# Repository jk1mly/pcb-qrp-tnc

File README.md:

# pcb-qrp-tnc
おもちゃのトランシーバ用のIC;BK4802Pを使ったモノバンドのFX.25対応TNC付き無線機
TNC部分はM5stamp

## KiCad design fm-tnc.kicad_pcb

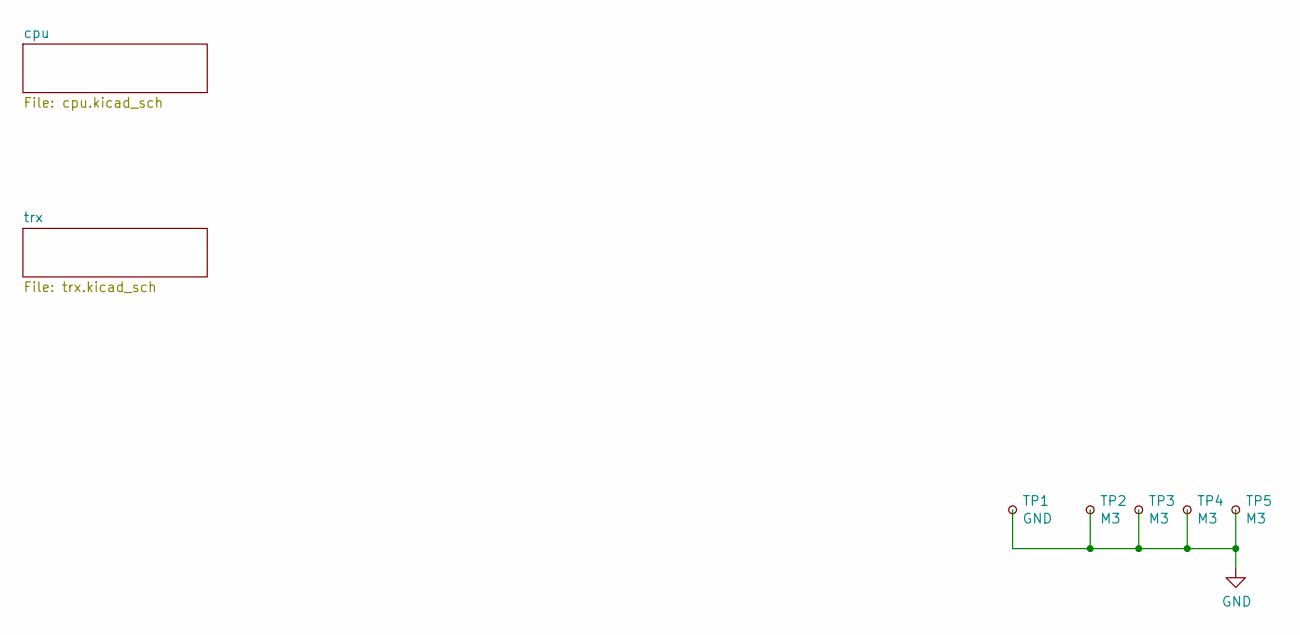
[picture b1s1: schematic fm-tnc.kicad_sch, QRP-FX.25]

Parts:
TP1: GND; PinHeader_1x01_P2.54mm_Vertical
TP2, TP3, TP4, TP5: M3; MountingHole_3.5mm_Pad

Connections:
GND: TP1.1, TP2.1, TP3.1, TP4.1, TP5.1; also elsewhere on the board

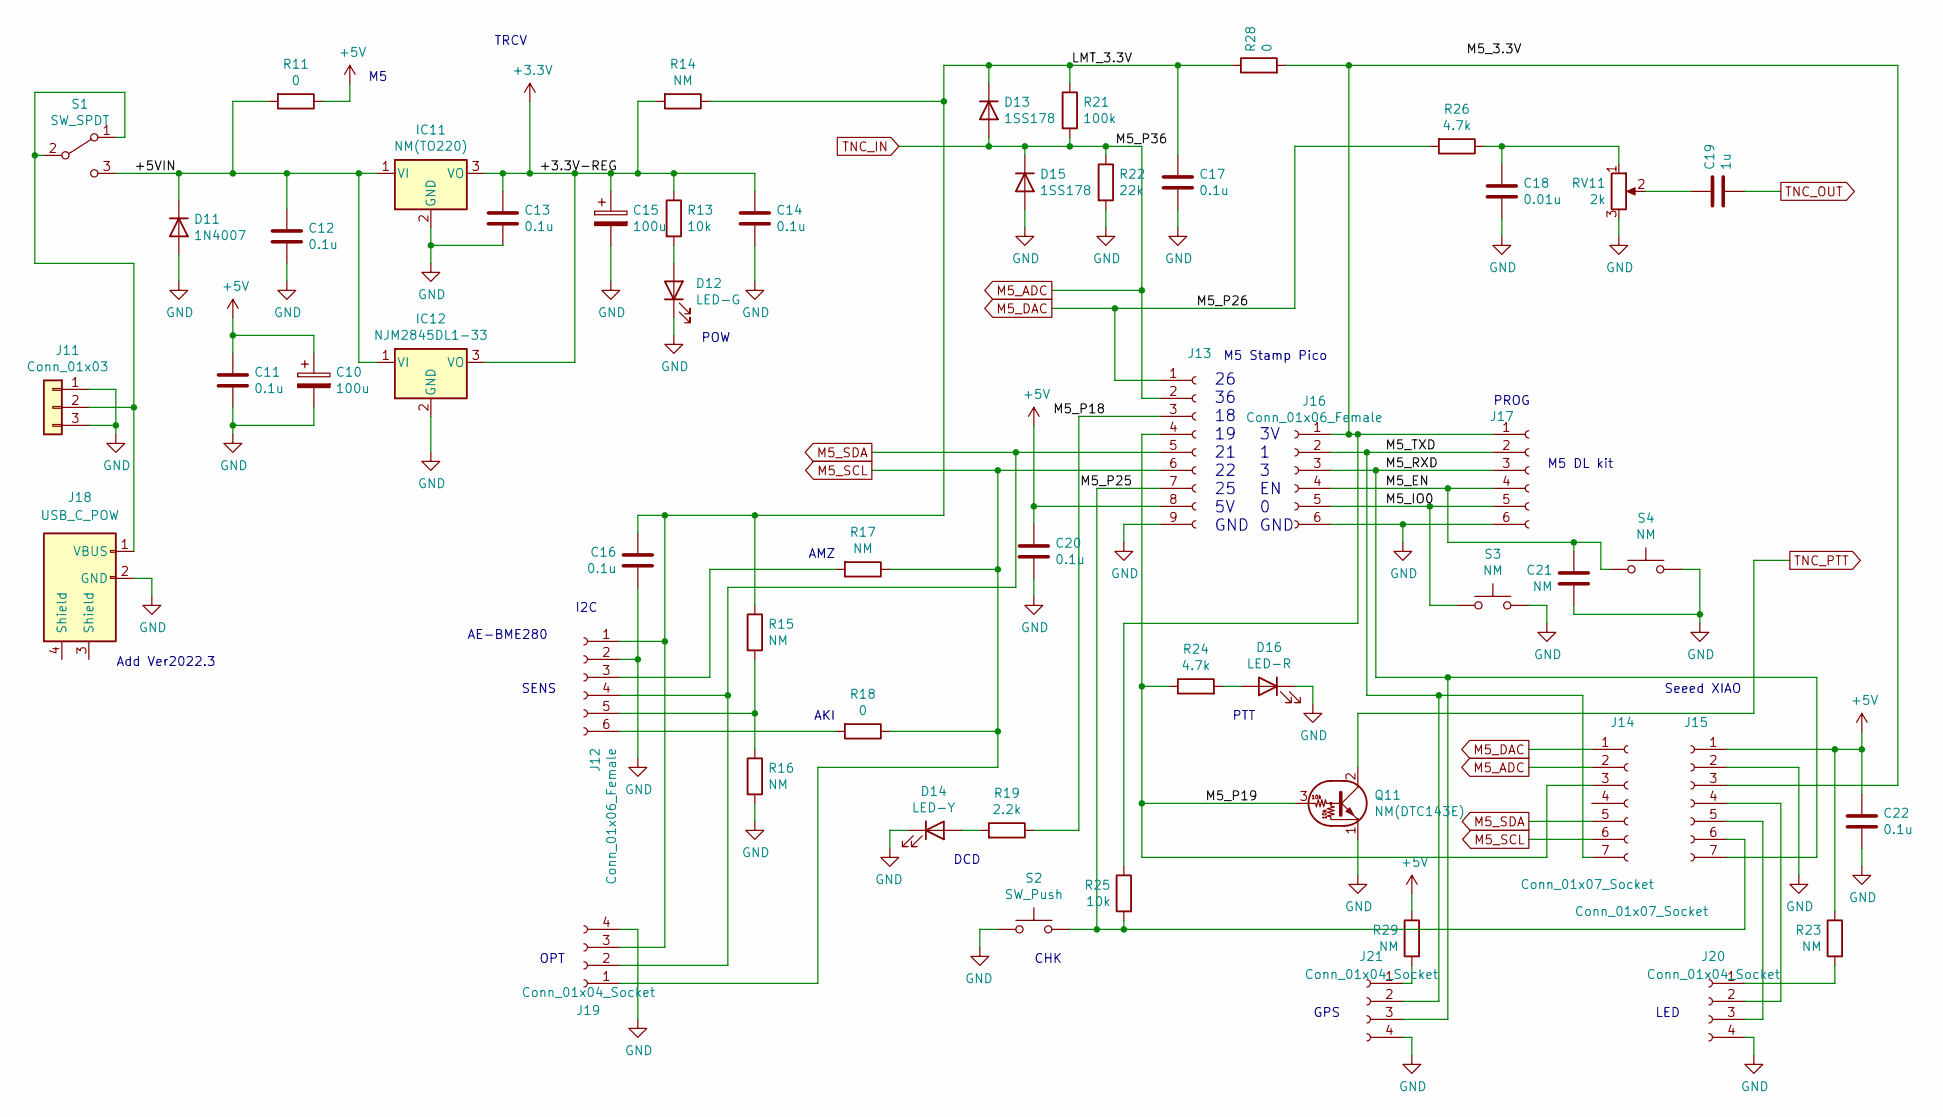
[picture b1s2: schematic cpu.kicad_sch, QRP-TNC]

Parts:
C10, C15: 100u; CP_Radial_D4.0mm_P2.00mm
C11, C12, C13, C14, C16, C17, C20, C22: 0.1u; C_Disc_D3.4mm_W2.1mm_P2.50mm
C18: 0.01u; C_Disc_D3.4mm_W2.1mm_P2.50mm
C19: 1u; C_Disc_D3.4mm_W2.1mm_P2.50mm
C21: NM; C_Disc_D3.4mm_W2.1mm_P2.50mm
D11: 1N4007; D_DO-41_SOD81_P10.16mm_Horizontal
D12: LED-G; LED_3mm_Radial
D13, D15: 1SS178; D_A-405_P2.54mm_Vertical_AnodeUp
D14: LED-Y; LED_3mm_Radial
D16: LED-R; LED_3mm_Radial
IC11: NM(TO220); TO-126-3_Vertical
IC12: NJM2845DL1-33; TO-252-3
J11: Conn_01x03; PinHeader_1x03_P2.54mm_Vertical
J12, J16, J17: Conn_01x06_Female; PinHeader_1x06_P2.54mm_Vertical
J13: Conn_01x09_Female; PinHeader_1x09_P2.54mm_Vertical
J14, J15: Conn_01x07_Socket; PinHeader_1x07_P2.54mm_Vertical
J18: USB_C_POW
J19, J20, J21: Conn_01x04_Socket; PinHeader_1x04_P2.54mm_Vertical
Q11: NM(DTC143E); TO-92_Inline_Wide
R11, R18, R28: 0; R_Axial_DIN0207_L6.3mm_D2.5mm_P2.54mm_Vertical
R13, R25: 10k; R_Axial_DIN0207_L6.3mm_D2.5mm_P2.54mm_Vertical
R14, R15, R16, R17, R23, R29: NM; R_Axial_DIN0207_L6.3mm_D2.5mm_P2.54mm_Vertical
R19: 2.2k; R_Axial_DIN0207_L6.3mm_D2.5mm_P2.54mm_Vertical
R21: 100k; R_Axial_DIN0207_L6.3mm_D2.5mm_P2.54mm_Vertical
R22: 22k; R_Axial_DIN0207_L6.3mm_D2.5mm_P2.54mm_Vertical
R24, R26: 4.7k; R_Axial_DIN0207_L6.3mm_D2.5mm_P2.54mm_Vertical
RV11: 2k; Potentiometer_Bourns_3386P_Vertical
S1: SW_SPDT; Switch_Slide_11.6x4mm_EG1218
S2: SW_Push; Switch_2P
S3, S4: NM; Switch_2P

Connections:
+3V3: C13.1, C14.1, C15.1, IC11.3 (VO), IC12.3 (VO), R13.1, R14.2; also elsewhere on the board
+5V: C10.1, C11.1, C20.1, C22.1, J13.8, J15.1, R11.1, R23.1, R29.1
/cpu/+5VIN: C12.1, D11.1 (K), IC11.1 (VI), IC12.1 (VI), R11.2, S1.3 (C)
/cpu/LMT_3.3V: C16.1, C17.1, D13.1 (K), J12.1, J19.3, R14.1, R15.1, R21.1, R28.1
/cpu/M5_EN: C21.1, J16.4, J17.4, S4.1
/cpu/M5_IO0: J16.5, J17.5, S3.1
/cpu/M5_P18: J13.3, R19.1
/cpu/M5_P19: J13.4, J14.3, Q11.3 (B), R24.1
/cpu/M5_P25: J13.7, J15.6, R25.2, S2.1
/cpu/M5_RXD: J15.7, J16.3, J17.3, J21.3
/cpu/M5_TXD: J14.7, J16.2, J17.2, J21.2
GND: C10.2, C11.2, C12.2, C13.2, C14.2, C15.2, C16.2, C17.2, C18.2, C20.2, C21.2, C22.2, D11.2 (A), D12.1 (K), D14.1 (K), D15.2 (A), D16.1 (K), IC11.2 (GND), IC12.2 (GND), J11.1, J11.3, J12.2, J13.9, J15.2, J16.6, J17.6, J18.2 (GND), J19.4, J20.4, J21.4, Q11.1 (E), R16.2, R22.2, RV11.3, S2.2, S3.2, S4.2; also elsewhere on the board
M5_ADC: D13.2 (A), D15.1 (K), J13.2, J14.2, R21.2, R22.1; also elsewhere on the board
M5_DAC: J13.1, J14.1, R26.2
M5_SCL: J13.6, J14.6, J19.1, R17.1, R18.1; also elsewhere on the board
M5_SDA: J12.4, J13.5, J14.5, J19.2; also elsewhere on the board
unnamed: C18.1, R26.1, RV11.1
unnamed: C19.1, RV11.2
unnamed: D12.2 (A), R13.2
unnamed: D14.2 (A), R19.2
unnamed: D16.2 (A), R24.2
unnamed: J11.2, J18.1 (VBUS), S1.1 (A), S1.2 (B)
unnamed: J12.3, R17.2
unnamed: J12.5, R15.2, R16.1
unnamed: J12.6, R18.2
unnamed: J15.3, J16.1, J17.1, R25.1, R28.2
unnamed: J15.4, J20.2
unnamed: J15.5, J20.3
unnamed: J20.1, R23.2
unnamed: J21.1, R29.2
TNC_OUT: C19.2; also elsewhere on the board
TNC_PTT: Q11.2 (C); also elsewhere on the board

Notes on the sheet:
DCD
PTT
SENS
OPT
AKI
CHK
3V 1 3 EN 0 GND
AMZ
26 36 18 19 21 22 25 5V GND
AE-BME280
M5 Stamp Pico
Add Ver2022.3
PROG
I2C
POW
TRCV
Seeed XIAO
M5 DL kit
GPS
LED

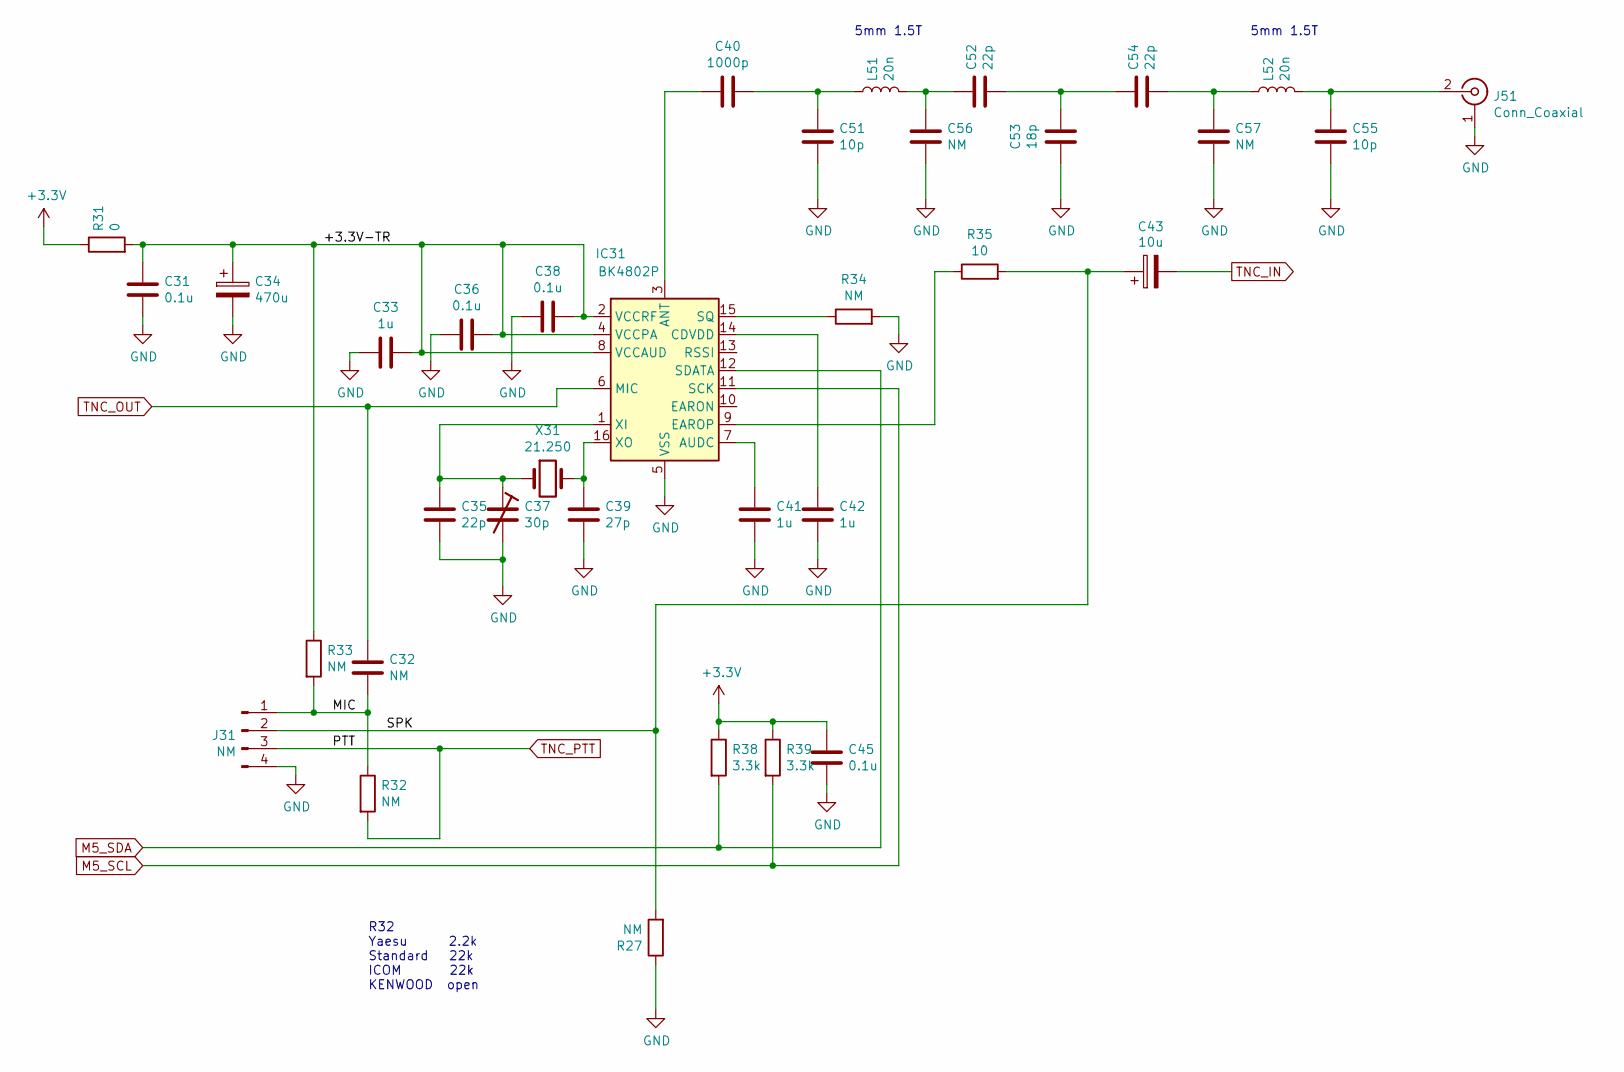
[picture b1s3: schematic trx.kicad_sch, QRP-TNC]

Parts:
C31, C36, C38, C45: 0.1u; C_Disc_D3.4mm_W2.1mm_P2.50mm
C32, C56, C57: NM; C_Disc_D3.4mm_W2.1mm_P2.50mm
C33, C41, C42: 1u; C_Disc_D3.4mm_W2.1mm_P2.50mm
C34: 470u; CP_Radial_D8.0mm_P3.50mm
C35, C52, C54: 22p; C_Disc_D3.4mm_W2.1mm_P2.50mm
C37: 30p; C_TRIM_P6.00mm
C39: 27p; C_Disc_D3.4mm_W2.1mm_P2.50mm
C40: 1000p; C_Disc_D3.4mm_W2.1mm_P2.50mm
C43: 10u; CP_Radial_D5.0mm_P2.00mm
C51, C55: 10p; C_Disc_D3.4mm_W2.1mm_P2.50mm
C53: 18p; C_Disc_D3.4mm_W2.1mm_P2.50mm
IC31: BK4802P; SO-16_3.9x9.9mm_P1.27mm
J31: NM; PinHeader_1x04_P2.54mm_Vertical
J51: Conn_Coaxial; RF_SMA_Vertical_5-1814832-1
L51, L52: 20n; coil3_7mm
R27, R32, R33, R34: NM; R_Axial_DIN0207_L6.3mm_D2.5mm_P2.54mm_Vertical
R31: 0; R_Axial_DIN0207_L6.3mm_D2.5mm_P2.54mm_Vertical
R35: 10; R_Axial_DIN0207_L6.3mm_D2.5mm_P2.54mm_Vertical
R38, R39: 3.3k; R_Axial_DIN0207_L6.3mm_D2.5mm_P2.54mm_Vertical
X31: 21.250; HC49

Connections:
+3V3: C45.1, R31.1, R38.1, R39.1; also elsewhere on the board
/trx/+3.3V-TR: C31.1, C33.2, C34.1, C36.2, C38.2, IC31.2 (VCCRF), IC31.4 (VCCPA), IC31.8 (VCCAUD), R31.2, R33.1
/trx/MIC: C32.2, J31.1, R32.1, R33.2
/trx/SPK: C43.1, J31.2, R27.2, R35.2
GND: C31.2, C33.1, C34.2, C35.2, C36.1, C37.2, C38.1, C39.2, C41.2, C42.2, C45.2, C51.2, C53.1, C55.2, C56.2, C57.2, IC31.5 (VSS), J31.4, J51.1 (G), R27.1, R34.2; also elsewhere on the board
M5_ADC: C43.2; also elsewhere on the board
M5_SCL: IC31.11 (SCK), R39.2; also elsewhere on the board
M5_SDA: IC31.12 (SDATA), R38.2; also elsewhere on the board
unnamed: C40.2, C51.1, L51.1
unnamed: C52.1, C56.1, L51.2
unnamed: C52.2, C53.2, C54.1
unnamed: C54.2, C57.1, L52.1
unnamed: C40.1, IC31.3 (ANT)
unnamed: C41.1, IC31.7 (AUDC)
unnamed: C42.1, IC31.14 (CDVDD)
unnamed: IC31.9 (EAROP), R35.1
unnamed: IC31.15 (SQ), R34.1
unnamed: C35.1, C37.1, IC31.1 (XI), X31.1
unnamed: C39.1, IC31.16 (XO), X31.2
unnamed: C55.1, J51.2 (S), L52.2
TNC_OUT: C32.1, IC31.6 (MIC); also elsewhere on the board
TNC_PTT: J31.3, R32.2; also elsewhere on the board

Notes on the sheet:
R32 Yaesu 2.2k Standard 22k ICOM 22k KENWOOD open
5mm 1.5T

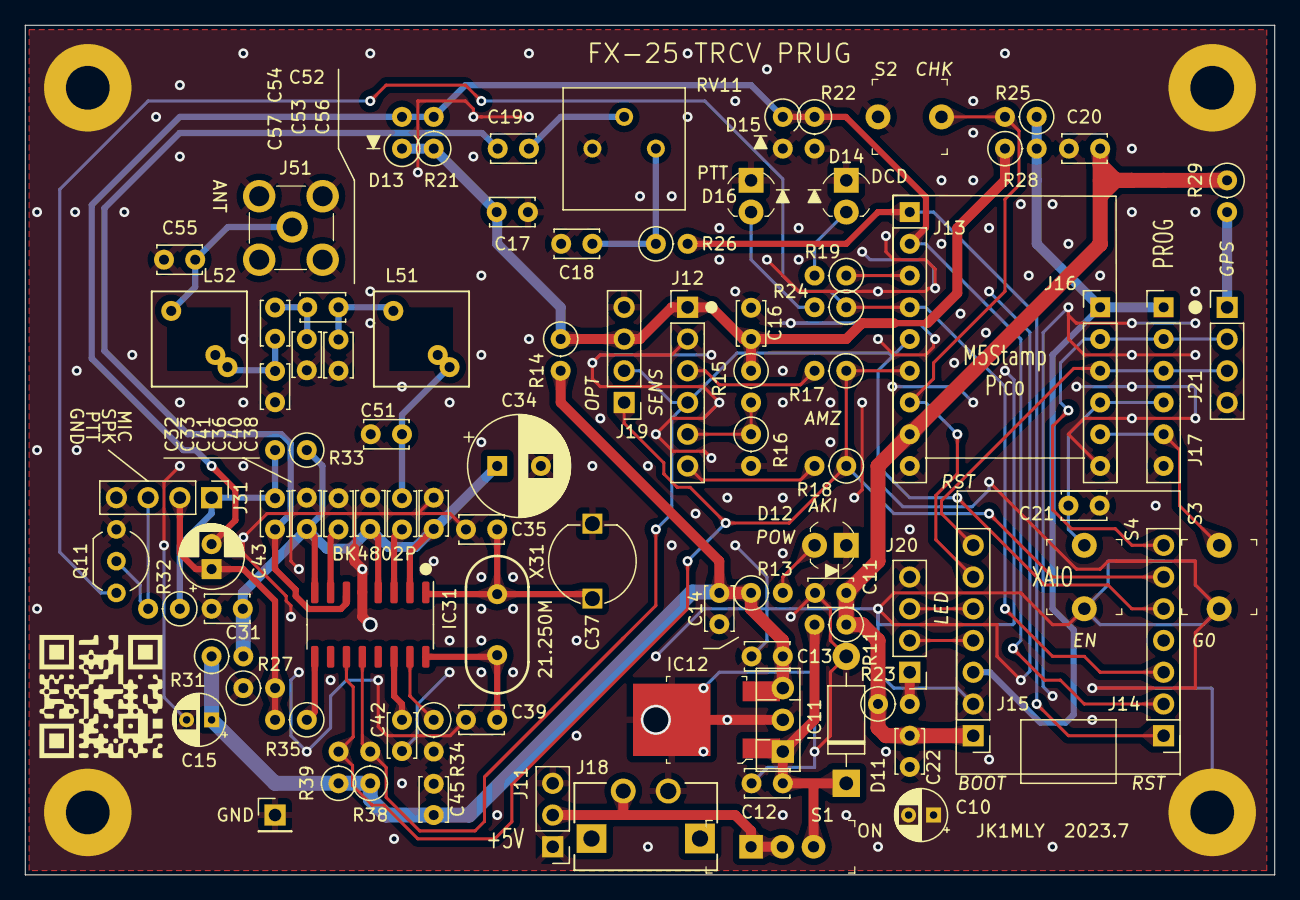
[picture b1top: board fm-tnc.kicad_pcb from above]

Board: 2 copper layers, 100.0 x 68.0 mm, 94 parts (0 on the bottom side), 47 nets.

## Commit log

2022-03-08 trial
2022-03-21 qrp-fm試作の反映
2022-03-21 fm-qrp試作の反映
2022-03-21 old version
2022-05-03 製作方法
2022-05-03 Add files via upload
    秋月の通販コード追加
    部品表の代わりにxmlファイルを追加
2022-05-14 バンドパスフィルタ見直し
2023-06-25 Add files via upload
    部品表
    Datasheet欄にP-12345とか入っているのは秋月
2023-07-17 assembly
2023-08-06 CAD data update
    CADデータを更新
2023-08-06 Add files via upload
    1つ忘れていたので追加
2023-08-06 製作の説明 ドラフト版を追加
